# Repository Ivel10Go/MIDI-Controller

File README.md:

# 🎹 MIDI Controller PCB
 
> A custom MIDI keyboard PCB built as part of the [Hackclub Blueprint](https://blueprint.hackclub.com/starter-projects/midi) program.

---
 
## Overview
 
This is a fully custom MIDI controller PCB featuring a mechanical switch matrix, per-key RGB lighting, rotary encoders, a high-quality audio DAC, and an ST7735R display — all driven by a Raspberry Pi Pico (Orpheus Pico).
 
<!-- Add more photos here — front/back of PCB, schematic screenshot, 3D render, etc. -->
<!--  -->
<!--  -->

---
 
## Features
 
- **38 mechanical keys** in a switch matrix (with 1N4148 diodes for anti-ghosting)
- **38 SK6812MINI-E RGB LEDs** — per-key addressable RGB lighting
- **2 rotary encoders** (Alps EC11E) with clickable push switch
- **PCM5102A audio DAC** with 3.5mm stereo output via I²S
- **ST7735R 1.8" TFT display** via SPI
- **MCP23017 I²C GPIO expander** for the key matrix
- **Raspberry Pi Pico (Orpheus Pico)** as the main microcontroller
- USB powered (5V via Pico)
- M3 and M2.5 mounting holes for case attachment
 
---

##Case

 I decided to go with an open design because I really like the look of the PCB. Thanks to [Miraculix50](https://github.com/Miraculix50) for the help.

# BOM
Bill of Materials:

Qty. | Item
:-:|:-:
1 | Orpheus Pico
38 | Cherry MX Switch
38 | Keycaps
1 | ST7735R LCD
38 | 1N4148
37 | SK6812 MINI LEDs
2 | EC11 rotary encoders
1 | PCM5100 IIS DAC
1 | MCP23017 I/O Expander
1 | PJ-320A 3.5mm TRRS Audio Jack
2 | 4,7 kΩ
2 | 10 kΩ

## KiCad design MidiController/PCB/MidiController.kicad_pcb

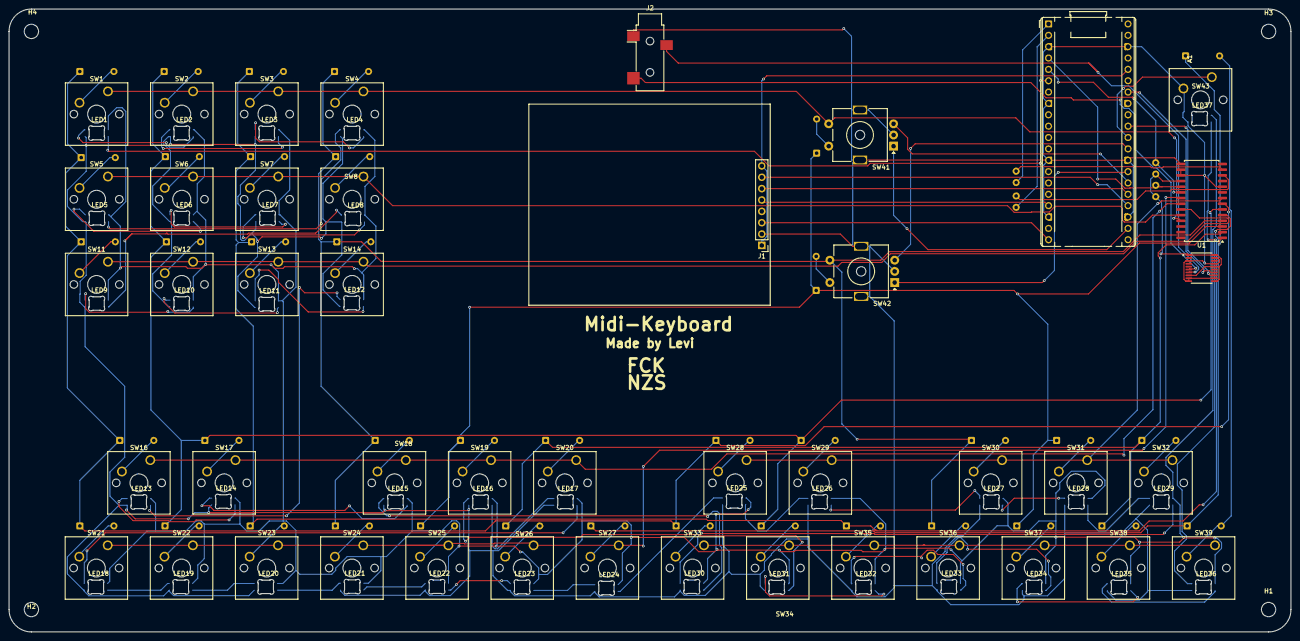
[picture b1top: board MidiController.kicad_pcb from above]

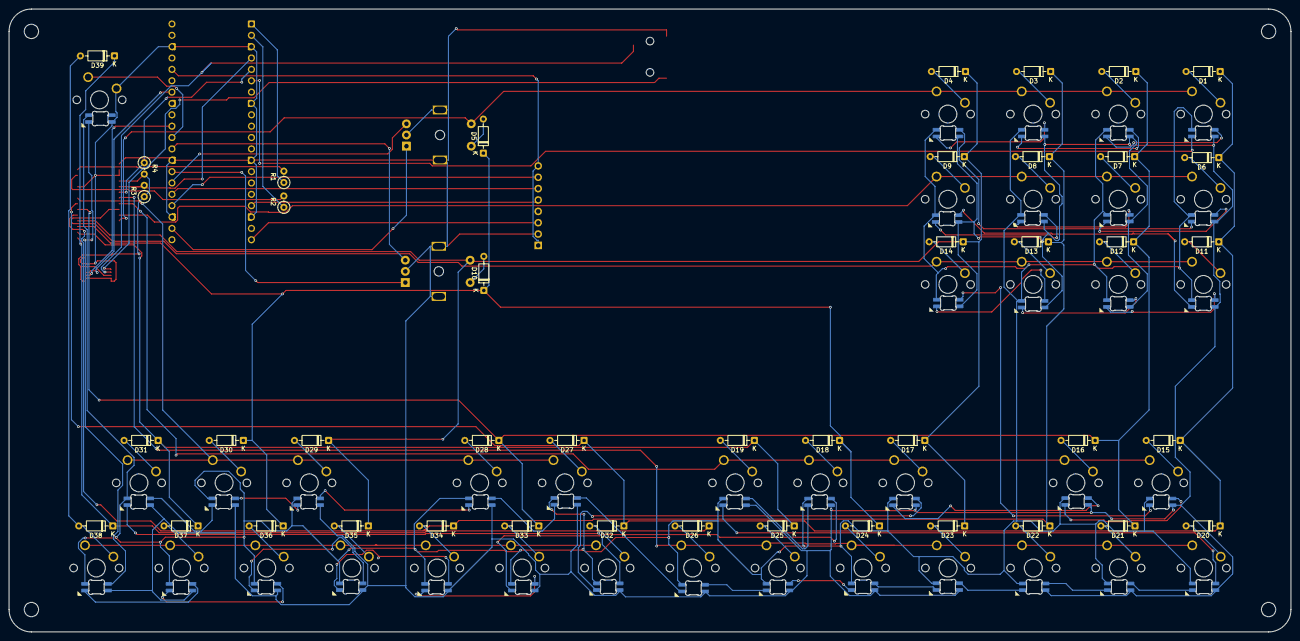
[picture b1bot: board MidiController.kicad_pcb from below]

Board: 2 copper layers, 286.6 x 139.3 mm, 128 parts (43 on the bottom side), 112 nets.

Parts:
A1: RaspberryPi_Pico; RaspberryPi_Pico_Common_THT
D1, D2, D3, D4, D5, D6, D7, D8, D9, D10, D11, D12, D13, D14, D15, D16, D17, D18, D19, D20, D21, D22, D23, D24, D25, D26, D27, D28, D29, D30, D31, D32, D33, D34, D35, D36, D37, D38, D39: 1N4148; D_DO-35_SOD27_P7.62mm_Horizontal
H1, H2, H3, H4: MountingHole; MountingHole_3.2mm_M3
J1: ST7735R; PinHeader_1x08_P2.54mm_Vertical
J2: AudioJack3; Jack_3.5mm_CUI_SJ-3523-SMT_Horizontal
LED1, LED2, LED3, LED4, LED5, LED6, LED7, LED8, LED9, LED10, LED11, LED12, LED13, LED14, LED15, LED16, LED17, LED18, LED19, LED20, LED21, LED22, LED23, LED24, LED25, LED26, LED27, LED28, LED29, LED30, LED31, LED32, LED33, LED34, LED35, LED36, LED37: SK6812MINI; SK6812MINI-E_fixed
R1, R2: 4.7k; R_Axial_DIN0207_L6.3mm_D2.5mm_P2.54mm_Vertical
R3, R4: 10k; R_Axial_DIN0207_L6.3mm_D2.5mm_P2.54mm_Vertical
SW1, SW2, SW3, SW4, SW5, SW6, SW7, SW8, SW11, SW12, SW13, SW14, SW16, SW17, SW18, SW19, SW20, SW21, SW22, SW23, SW24, SW25, SW26, SW27, SW28, SW29, SW30, SW31, SW32, SW33, SW34, SW35, SW36, SW37, SW38, SW39, SW43: SW_Push_45deg; SW_Cherry_MX_1.00u_PCB
SW41, SW42: RotaryEncoder_Switch_MP; RotaryEncoder_Alps_EC11E-Switch_Vertical_H20mm_MountingHoles
U1: MCP23017_SO; SOIC-28W_7.5x17.9mm_P1.27mm
U2: PCM5100; TSSOP-20_4.4x6.5mm_P0.65mm

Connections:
1A: A1.22 (GPIO17), SW41.A
1B: A1.26 (GPIO20), SW41.B
1S1: SW1.1, SW2.1, SW3.1, SW4.1, SW41.S1, U1.25 (GPA4)
1S2: D5.2 (A), SW41.S2
2A: A1.27 (GPIO21), SW42.A
2B: A1.29 (GPIO22), SW42.B
2S1: D4.1 (K), D9.1 (K), D14.1 (K), D17.1 (K), D23.1 (K), D29.1 (K), D35.1 (K), SW42.S1, U1.4 (GPB3)
2S2: D10.2 (A), SW42.S2
+3.3V: A1.36 (3V3), J1.1, J1.8
+3V3: R3.1, R4.2, U1.18 (~RESET), U2.1 (CPVDD), U2.8 (AVDD), U2.11 (FLT), U2.16 (FMT), U2.20 (DVDD)
+5V: LED1.4 (VDD), LED2.4 (VDD), LED3.4 (VDD), LED4.4 (VDD), LED5.4 (VDD), LED6.4 (VDD), LED7.4 (VDD), LED8.4 (VDD), LED9.4 (VDD), LED10.4 (VDD), LED11.4 (VDD), LED12.4 (VDD), LED13.4 (VDD), LED14.4 (VDD), LED15.4 (VDD), LED16.4 (VDD), LED17.4 (VDD), LED18.4 (VDD), LED19.4 (VDD), LED20.4 (VDD), LED21.4 (VDD), LED22.4 (VDD), LED23.4 (VDD), LED24.4 (VDD), LED25.4 (VDD), LED26.4 (VDD), LED27.4 (VDD), LED28.4 (VDD), LED29.4 (VDD), LED30.4 (VDD), LED31.4 (VDD), LED32.4 (VDD), LED33.4 (VDD), LED34.4 (VDD), LED35.4 (VDD), LED36.4 (VDD), LED37.4 (VDD)
A0: A1.17 (GPIO13), J1.5
BLCK: A1.31 (GPIO26_ADC0), U2.13 (BCK)
COL0: D1.1 (K), D6.1 (K), D11.1 (K), D15.1 (K), D20.1 (K), D27.1 (K), D32.1 (K), U1.7 (GPB6)
COL1: D2.1 (K), D7.1 (K), D12.1 (K), D16.1 (K), D21.1 (K), D28.1 (K), D33.1 (K), U1.6 (GPB5)
COL2: D3.1 (K), D8.1 (K), D13.1 (K), D22.1 (K), D34.1 (K), U1.5 (GPB4)
COL4: D5.1 (K), D10.1 (K), D18.1 (K), D24.1 (K), D30.1 (K), D36.1 (K), U1.3 (GPB2)
COL5: D19.1 (K), D25.1 (K), D31.1 (K), D37.1 (K), U1.2 (GPB1)
COL6: D26.1 (K), D38.1 (K), D39.1 (K), U1.1 (GPB0)
CS_LCD: A1.20 (GPIO15), J1.3
DIN: A1.34 (GPIO28_ADC2), U2.14 (DIN)
GND: A1.3 (GND), A1.8 (GND), A1.13 (GND), A1.18 (GND), A1.23 (GND), A1.28 (GND), A1.38 (GND), J1.2, J2.S, LED1.2 (VSS), LED2.2 (VSS), LED3.2 (VSS), LED4.2 (VSS), LED5.2 (VSS), LED6.2 (VSS), LED7.2 (VSS), LED8.2 (VSS), LED9.2 (VSS), LED10.2 (VSS), LED11.2 (VSS), LED12.2 (VSS), LED13.2 (VSS), LED14.2 (VSS), LED15.2 (VSS), LED16.2 (VSS), LED17.2 (VSS), LED18.2 (VSS), LED19.2 (VSS), LED20.2 (VSS), LED21.2 (VSS), LED22.2 (VSS), LED23.2 (VSS), LED24.2 (VSS), LED25.2 (VSS), LED26.2 (VSS), LED27.2 (VSS), LED28.2 (VSS), LED29.2 (VSS), LED30.2 (VSS), LED31.2 (VSS), LED32.2 (VSS), LED33.2 (VSS), LED34.2 (VSS), LED35.2 (VSS), LED36.2 (VSS), LED37.2 (VSS), SW41.C, SW41.MP, SW42.C, SW42.MP, SW43.2, U1.10 (VSS), U1.15 (A0), U1.16 (A1), U1.17 (A2), U2.3 (CPGND), U2.9 (AGND), U2.10 (DEMP), U2.12 (SCK), U2.17 (XSMT), U2.19 (DGND)
GPIOSCL: A1.2 (GPIO1), R2.1
GPIOSDA: A1.1 (GPIO0), R1.1
INTA: A1.4 (GPIO2), R3.2, U1.19 (INTB)
INTB: A1.5 (GPIO3), R4.1, U1.20 (INTA)
LED_DATA: A1.6 (GPIO4), LED1.3 (DIN)
MOSI: A1.25 (GPIO19), J1.6
unnamed: A1.30 (RUN), SW43.1
unnamed: D1.2 (A), SW1.2
unnamed: D2.2 (A), SW2.2
unnamed: D3.2 (A), SW3.2
unnamed: D4.2 (A), SW4.2
unnamed: D6.2 (A), SW5.2
unnamed: D7.2 (A), SW6.2
unnamed: D8.2 (A), SW7.2
unnamed: D9.2 (A), SW8.2
unnamed: D11.2 (A), SW11.2
unnamed: D12.2 (A), SW12.2
unnamed: D13.2 (A), SW13.2
unnamed: D14.2 (A), SW14.2
unnamed: D15.2 (A), SW16.2
unnamed: D16.2 (A), SW17.2
unnamed: D17.2 (A), SW18.2
unnamed: D18.2 (A), SW19.2
unnamed: D19.2 (A), SW20.2
unnamed: D20.2 (A), SW21.2
unnamed: D21.2 (A), SW22.2
unnamed: D22.2 (A), SW23.2
unnamed: D23.2 (A), SW24.2
unnamed: D24.2 (A), SW25.2
unnamed: D25.2 (A), SW26.2
unnamed: D26.2 (A), SW27.2
unnamed: D27.2 (A), SW28.2
unnamed: D28.2 (A), SW29.2
unnamed: D29.2 (A), SW30.2
unnamed: D30.2 (A), SW31.2
unnamed: D31.2 (A), SW32.2
unnamed: D32.2 (A), SW33.2
unnamed: D33.2 (A), SW34.2
unnamed: D34.2 (A), SW35.2
unnamed: D35.2 (A), SW36.2
unnamed: D36.2 (A), SW37.2
unnamed: D37.2 (A), SW38.2
unnamed: D38.2 (A), D39.2 (A), SW39.2
unnamed: LED1.1 (DOUT), LED2.3 (DIN)
unnamed: LED2.1 (DOUT), LED3.3 (DIN)
unnamed: LED3.1 (DOUT), LED4.3 (DIN)
unnamed: LED4.1 (DOUT), LED5.3 (DIN)
unnamed: LED5.1 (DOUT), LED6.3 (DIN)
unnamed: LED6.1 (DOUT), LED7.3 (DIN)
unnamed: LED7.1 (DOUT), LED8.3 (DIN)
unnamed: LED8.1 (DOUT), LED9.3 (DIN)
unnamed: LED9.1 (DOUT), LED10.3 (DIN)
unnamed: LED10.1 (DOUT), LED11.3 (DIN)
unnamed: LED11.1 (DOUT), LED12.3 (DIN)
unnamed: LED12.1 (DOUT), LED13.3 (DIN)
unnamed: LED13.1 (DOUT), LED14.3 (DIN)
unnamed: LED14.1 (DOUT), LED15.3 (DIN)
unnamed: LED15.1 (DOUT), LED30.3 (DIN)
unnamed: LED16.3 (DIN), LED17.1 (DOUT)
unnamed: LED16.1 (DOUT), LED31.3 (DIN)
unnamed: LED17.3 (DIN), LED18.1 (DOUT)
unnamed: LED18.3 (DIN), LED19.1 (DOUT)
unnamed: LED19.3 (DIN), LED20.1 (DOUT)
unnamed: LED20.3 (DIN), LED21.1 (DOUT)
unnamed: LED21.3 (DIN), LED22.1 (DOUT)
unnamed: LED22.3 (DIN), LED23.1 (DOUT)
unnamed: LED23.3 (DIN), LED24.1 (DOUT)
unnamed: LED24.3 (DIN), LED25.1 (DOUT)
unnamed: LED25.3 (DIN), LED26.1 (DOUT)
unnamed: LED26.3 (DIN), LED27.1 (DOUT)
unnamed: LED27.3 (DIN), LED28.1 (DOUT)
unnamed: LED28.3 (DIN), LED29.1 (DOUT)
unnamed: LED29.3 (DIN), LED30.1 (DOUT)
unnamed: LED31.1 (DOUT), LED32.3 (DIN)
unnamed: LED32.1 (DOUT), LED33.3 (DIN)
unnamed: LED33.1 (DOUT), LED34.3 (DIN)
unnamed: LED34.1 (DOUT), LED35.3 (DIN)
unnamed: LED35.1 (DOUT), LED36.3 (DIN)
unnamed: LED36.1 (DOUT), LED37.3 (DIN)
unnamed: R2.2, U1.12 (SCK)
unnamed: R1.2, U1.13 (SDA)
OUTLEFT: J2.T, U2.6 (OUTL)
OUTRIGHT: J2.R, U2.7 (OUTR)
ROW1: SW5.1, SW6.1, SW7.1, SW8.1, U1.24 (GPA3)
ROW2: SW11.1, SW12.1, SW13.1, SW14.1, U1.23 (GPA2)
ROW3: SW16.1, SW17.1, SW18.1, SW19.1, SW20.1, U1.22 (GPA1)
ROW4: SW21.1, SW22.1, SW23.1, SW24.1, SW25.1, SW26.1, SW27.1, U1.21 (GPA0)
ROW5: SW28.1, SW29.1, SW30.1, SW31.1, SW32.1, U1.8 (GPB7)
ROW6: SW33.1, SW34.1, SW35.1, SW36.1, SW37.1, SW38.1, SW39.1
SCK: A1.24 (GPIO18), J1.7

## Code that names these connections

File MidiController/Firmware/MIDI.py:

# MIDI Controller Keyboard - CircuitPython
# Raspberry Pi Pico 2 + MCP23017 key matrix + ST7735 display + rotary encoders

import board
import busio
import digitalio
import time
import displayio
from fourwire import FourWire
from adafruit_st7735r import ST7735R
import adafruit_midi
from adafruit_midi.note_off import NoteOff
from adafruit_midi.note_on import NoteOn
from adafruit_midi.pitch_bend import PitchBend
from adafruit_midi.control_change import ControlChange
from adafruit_mcp230xx.mcp23017 import MCP23017
import rotaryio
import usb_midi

# ============ PIN ASSIGNMENTS (from KiCad schematic) ============
# I2C: GPIO0=SDA, GPIO1=SCL (MCP23017)
# SPI Display: GPIO18=SCK, GPIO19=MOSI, GPIO15=CS_LCD, GPIO13=A0/DC, GPIO8=RST
# Encoder 1: GPIO17=1A, GPIO20=1B
# Encoder 2: GPIO21=2A, GPIO22=2B
# I2S DAC: GPIO26=BLCK, GPIO27=LRCLK, GPIO28=DIN (optional - for future audio)

# ============ KEY MATRIX (MCP23017) ============
# Rows: GPA0, GPA1, GPA2, GPA3, GPA4, GPB7 (6 rows)
# Cols: GPB0, GPB1, GPB2, GPB3, GPB4, GPB5, GPB6 (7 cols)
# 6x7 = 42 keys | Rows 0-2: User buttons/encoders | Rows 3-6: Piano keys (low + high octave)

ROWS = 6
COLS = 7
NUM_KEYS = ROWS * COLS

# Base MIDI note (C2 = 36). Keys map to 36-77 (C2 to F5)
BASE_NOTE = 36
VELOCITY = 127

# Octave shift (0 = no shift, 12 = +1 octave, -12 = -1 octave)
octave_shift = 0

# ============ INITIALIZE I2C & MCP23017 ============
i2c = busio.I2C(board.GP0, board.GP1)
mcp = MCP23017(i2c)

# Create row pins (outputs) - GPA0-4, GPB7
row_pins = [
    mcp.get_pin(0),   # GPA0
    mcp.get_pin(1),   # GPA1
    mcp.get_pin(2),   # GPA2
    mcp.get_pin(3),   # GPA3
    mcp.get_pin(4),   # GPA4
    mcp.get_pin(15),  # GPB7
]
# Create column pins (inputs with pull-up) - GPB0-6
col_pins = [
    mcp.get_pin(8),   # GPB0
    mcp.get_pin(9),   # GPB1
    mcp.get_pin(10),  # GPB2
    mcp.get_pin(11),  # GPB3
    mcp.get_pin(12),  # GPB4
    mcp.get_pin(13),  # GPB5
    mcp.get_pin(14),  # GPB6
]

# Configure pins
for pin in row_pins:
    pin.switch_to_output(value=True)  # High = inactive
for pin in col_pins:
    pin.switch_to_input(pull=digitalio.Pull.UP)

# ============ KEY STATE (for debouncing) ============
key_state = [False] * NUM_KEYS

def scan_matrix():
    """Scan key matrix and return list of (key_number, pressed)."""
    events = []
    for row in range(ROWS):
        # Drive current row low
        row_pins[row].value = False
        time.sleep(0.001)  # Settling time
        # Read columns
        for col in range(COLS):
            key_num = row * COLS + col
            pressed = not col_pins[col].value  # Low = pressed (pull-up)
            if pressed != key_state[key_num]:
                key_state[key_num] = pressed
                events.append((key_num, pressed))
        # Drive row high again
        row_pins[row].value = True
    return events

# ============ ROTARY ENCODERS ============
encoder1 = rotaryio.IncrementalEncoder(board.GP17, board.GP20)
encoder2 = rotaryio.IncrementalEncoder(board.GP21, board.GP22)
enc1_pos = encoder1.position
enc2_pos = encoder2.position

# ============ DISPLAY ============
displayio.release_displays()
spi = busio.SPI(board.GP18, MOSI=board.GP19)
display_bus = FourWire(
    spi,
    command=board.GP13,
    chip_select=board.GP15,
    reset=board.GP8,
)
display = ST7735R(display_bus, width=128, height=160, rotation=270)

# Create main group and show
main_group = displayio.Group()
display.show(main_group)

# Simple splash text
text_area = None
try:
    from adafruit_display_text import label
    import terminalio
    text_area = label.Label(terminalio.FONT, text="MIDI Keyboard", color=0x00FF00)
    text_area.x = 10
    text_area.y = 70
    main_group.append(text_area)
except (ImportError, OSError):
    pass

# ============ MIDI ============
midi = adafruit_midi.MIDI(
    midi_in=usb_midi.ports[0],
    in_channel=0,
    midi_out=usb_midi.ports[1],
    out_channel=0,
)

# ============ MAIN LOOP ============
last_display_update = 0
pitch_bend_center = 8192  # 14-bit center
current_pitch_bend = pitch_bend_center

while True:
    # Scan keyboard matrix
    for key_num, pressed in scan_matrix():
        # Rows 0-2: control buttons (octave up/down, etc.)
        if key_num < 3 * COLS:  # First 3 rows = user buttons
            if pressed and key_num == 0:  # Octave down
                octave_shift = max(-24, octave_shift - 12)
            elif pressed and key_num == 1:  # Octave up
                octave_shift = min(24, octave_shift + 12)
            # Add more control mappings as needed
        else:
            # Rows 3-5: piano keys (low + high octave) - send MIDI
            midi_note = BASE_NOTE + (key_num - 3 * COLS) + octave_shift
            midi_note = max(0, min(127, midi_note))
            if pressed:
                midi.send(NoteOn(midi_note, VELOCITY))
            else:
                midi.send(NoteOff(midi_note, 0))

    # Encoder 1 = Pitch bend
    pos1 = encoder1.position
    if pos1 != enc1_pos:
        delta = pos1 - enc1_pos
        current_pitch_bend = max(0, min(16383, current_pitch_bend + delta * 400))
        midi.send(PitchBend(current_pitch_bend))
        enc1_pos = pos1

    # Encoder 2 = Modulation wheel (CC 1)
    pos2 = encoder2.position
    if pos2 != enc2_pos:
        delta = pos2 - enc2_pos
        mod_value = max(0, min(127, 64 + delta * 10))
        midi.send(ControlChange(1, mod_value))
        enc2_pos = pos2

    # Return pitch bend to center when encoder not moved (optional)
    # current_pitch_bend = pitch_bend_center  # Uncomment for spring-back

    # Update display periodically
    now = time.monotonic()
    if text_area and (now - last_display_update) > 0.5:
        text_area.text = f"Oct:{octave_shift//12:+d}"
        last_display_update = now

    time.sleep(0.01)  # ~100Hz scan rate

    #test

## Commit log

2026-03-28 Add BOM section to README
    Added a Bill of Materials section with itemized components.
2026-03-28 Revise README for MIDI Controller project
    Updated project title and added detailed overview and features of the MIDI controller PCB.
2026-03-28 Add images to README
    Added images to README for better visual representation.
2026-03-28 Remove 1 µF capacitor from the list
2026-03-28 Add case design section to README
    Added a section about the case design with images.
2026-03-28 Add keycaps to the item list in README
2026-03-28 Remove XIAO RP2040 from README components list
    Removed XIAO RP2040 from the components list.
2026-03-29 Add 3d directory for 3D files
2026-03-29 Add case .step file
2026-03-31 Add BOM.csv with component details and links
